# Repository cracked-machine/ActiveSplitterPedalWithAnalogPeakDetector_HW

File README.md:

## Active 4-way splitter pedal with analog peak detector

Required Kicad Hardware library: https://github.com/cracked-machine/KicadLibrary

- Analog 1->4 splitter circuit with buffered input and output gain controls.
- Analog LED peak detector per output channel.
- Fits in a Hammond 1590BB enclosure (120mm x 95mm).

### System Overview

### Schematic

##### Top Level

##### Power Supply block

##### Buffer/Attenuator block

##### Peak Detector block

## 3D Renderings

__PCB 3D Render (top view)__

__PCB 3D Render (bottom view)__

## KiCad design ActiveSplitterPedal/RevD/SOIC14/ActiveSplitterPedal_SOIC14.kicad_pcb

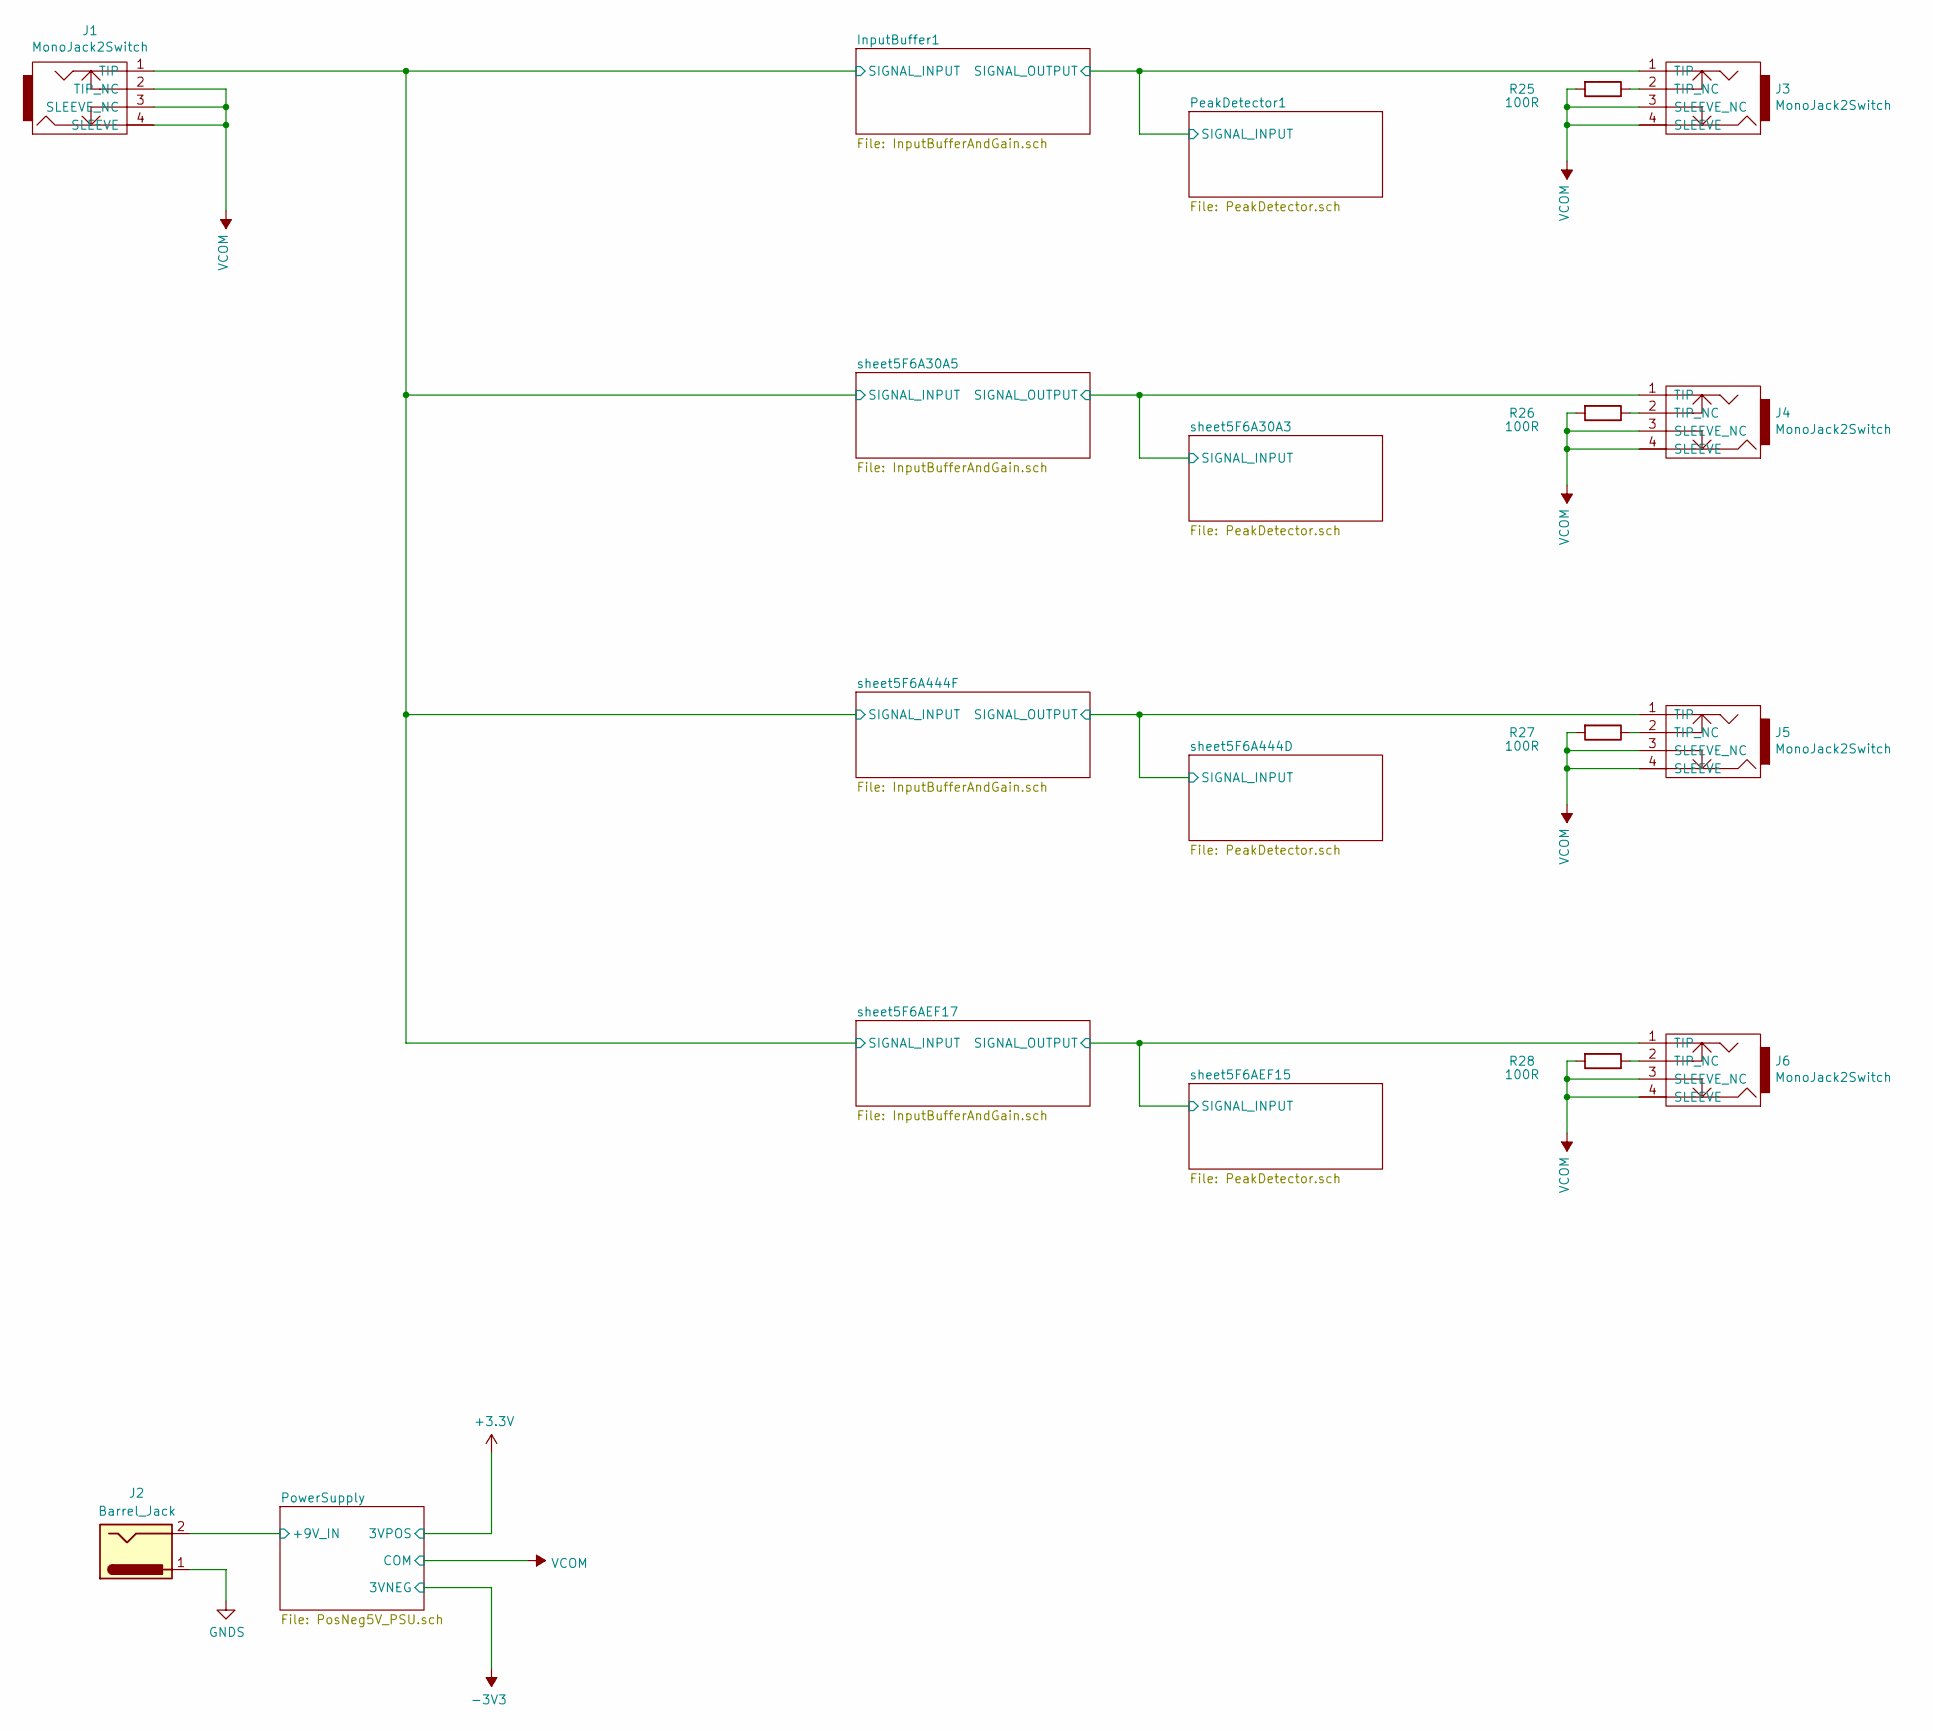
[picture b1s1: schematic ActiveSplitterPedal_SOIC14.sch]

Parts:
J1, J3, J4, J5, J6: MonoJack2Switch; NRJxHx
J2: Barrel_Jack; BarrelJack_Horizontal
R25, R26, R27, R28: 100R; C_0805_2012Metric_Pad1.15x1.40mm_HandSolder

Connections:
/InputBuffer1/SIGNAL_INPUT: J1.1 (TIP); also elsewhere on the board
/PeakDetector1/SIGNAL_INPUT: J3.1 (TIP); also elsewhere on the board
/PowerSupply/+9V_IN: J2.2; also elsewhere on the board
/sheet5F6A30A3/SIGNAL_INPUT: J4.1 (TIP); also elsewhere on the board
/sheet5F6A444D/SIGNAL_INPUT: J5.1 (TIP); also elsewhere on the board
/sheet5F6AEF15/SIGNAL_INPUT: J6.1 (TIP); also elsewhere on the board
GNDS: J2.1; also elsewhere on the board
unnamed: J3.2 (TIP_NC), R25.1
unnamed: J4.2 (TIP_NC), R26.1
unnamed: J5.2 (TIP_NC), R27.1
unnamed: J6.2 (TIP_NC), R28.1
VCOM: J1.2 (TIP_NC), J1.3 (SLEEVE_NC), J1.4 (SLEEVE), J3.3 (SLEEVE_NC), J3.4 (SLEEVE), J4.3 (SLEEVE_NC), J4.4 (SLEEVE), J5.3 (SLEEVE_NC), J5.4 (SLEEVE), J6.3 (SLEEVE_NC), J6.4 (SLEEVE), R25.2, R26.2, R27.2, R28.2; also elsewhere on the board

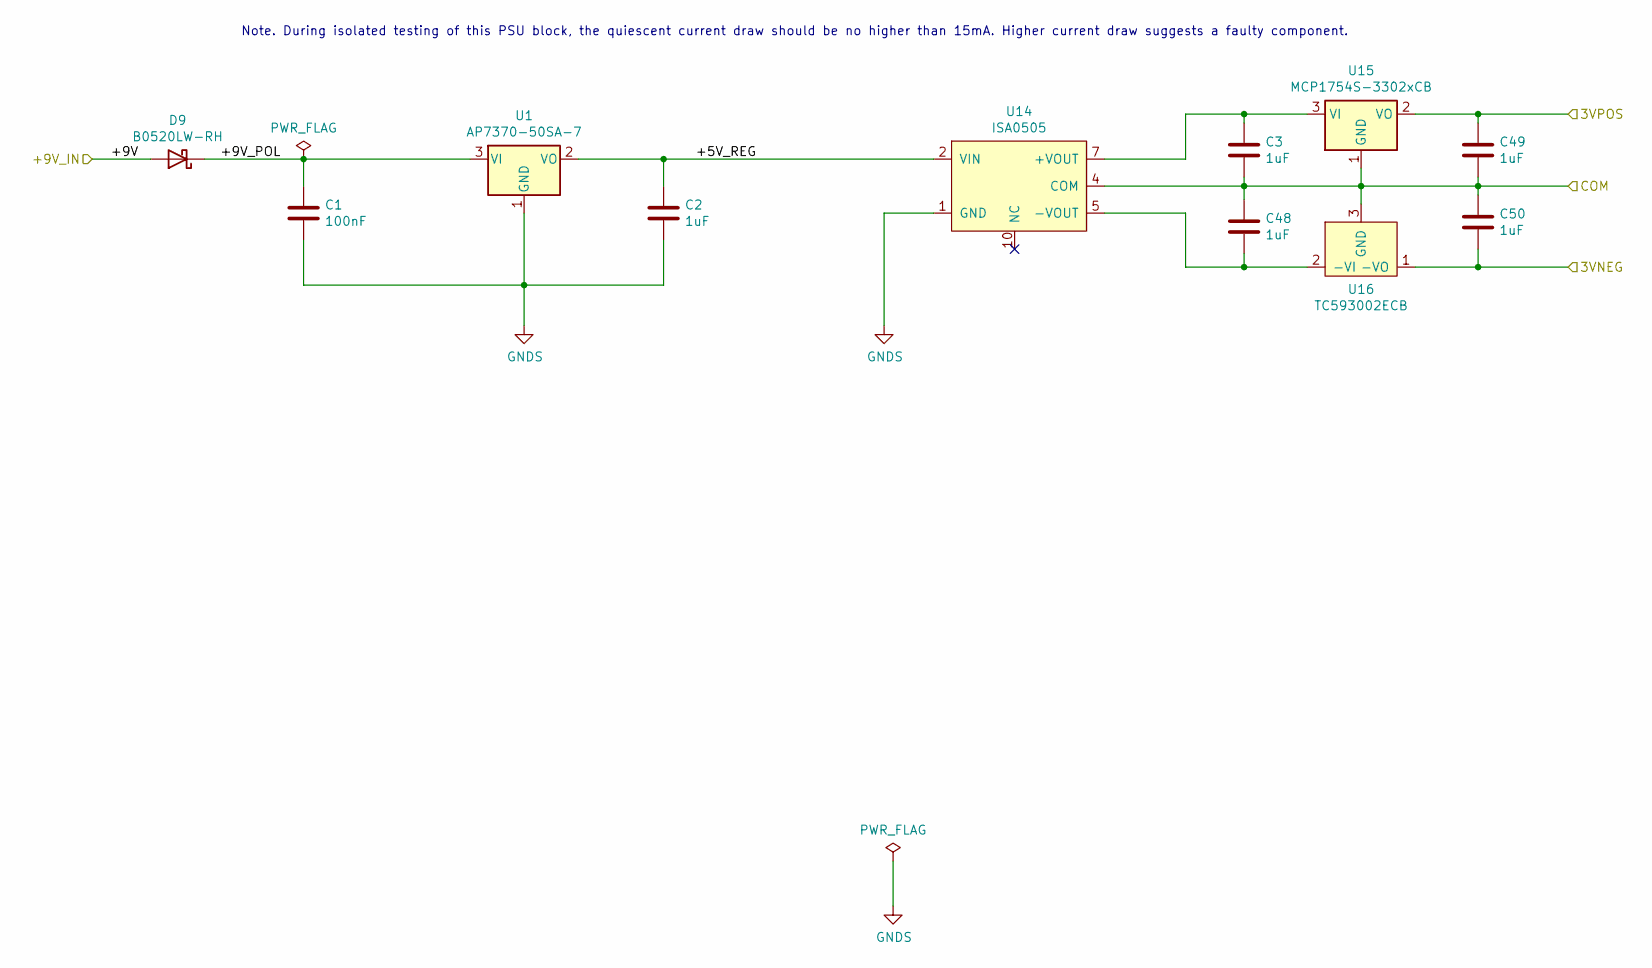
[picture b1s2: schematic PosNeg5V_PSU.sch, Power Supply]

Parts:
C1: 100nF; C_1206_3216Metric_Pad1.42x1.75mm_HandSolder
C2: 1uF; C_1206_3216Metric_Pad1.42x1.75mm_HandSolder
C3, C48, C49, C50: 1uF; C_0805_2012Metric_Pad1.15x1.40mm_HandSolder
D9: B0520LW-RH; D_SOD-123F
U1: AP7370-50SA-7; SOT-23
U14: ISA0505
U15: MCP1754S-3302xCB; SOT-23
U16: TC593002ECB; SOT-23

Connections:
+3V3: C49.1, U15.2 (VO); also elsewhere on the board
-3V3: C50.2, U16.1 (-VO); also elsewhere on the board
/PowerSupply/+5V_REG: C2.1, U1.2 (VO), U14.2 (VIN)
/PowerSupply/+9V_IN: D9.2 (A); also elsewhere on the board
/PowerSupply/+9V_POL: C1.1, D9.1 (K), U1.3 (VI)
GNDS: C1.2, C2.2, U1.1 (GND), U14.1 (GND); also elsewhere on the board
unnamed: C3.1, U14.7 (+VOUT), U15.3 (VI)
unnamed: C48.2, U14.5 (-VOUT), U16.2 (-VI)
VCOM: C3.2, C48.1, C49.2, C50.1, U14.4 (COM), U15.1 (GND), U16.3 (GND); also elsewhere on the board

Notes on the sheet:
Note. During isolated testing of this PSU block, the quiescent current draw should be no higher than 15mA. Higher current draw suggests a faulty component.

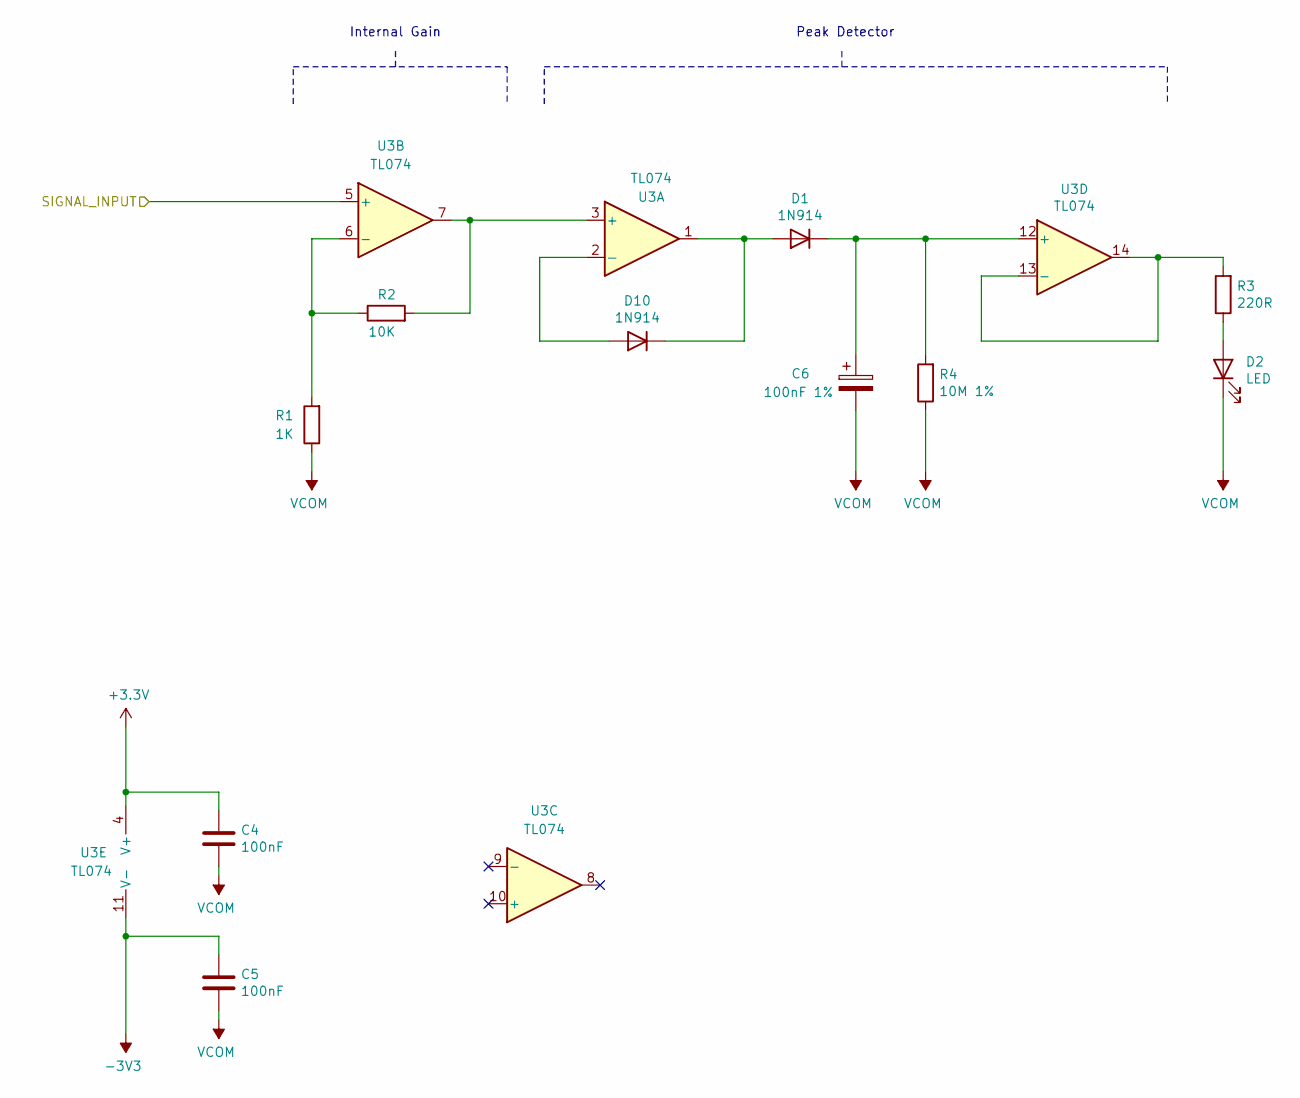
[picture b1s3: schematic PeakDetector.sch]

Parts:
C4, C5: 100nF; C_0805_2012Metric_Pad1.15x1.40mm_HandSolder
C6: 100nF 1%; C_1210_3225Metric_Pad1.42x2.65mm_HandSolder
D1, D10: 1N914; D_SOD-123F
D2: LED; LED_D5.0mm
R1: 1K; R_0805_2012Metric_Pad1.15x1.40mm_HandSolder
R2: 10K; R_0805_2012Metric_Pad1.15x1.40mm_HandSolder
R3: 220R; R_0805_2012Metric_Pad1.15x1.40mm_HandSolder
R4: 10M 1%; R_0805_2012Metric_Pad1.15x1.40mm_HandSolder
U3: TL074; SOIC-14_3.9x8.7mm_P1.27mm

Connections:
+3V3: C4.1, U3.4 (V+); also elsewhere on the board
-3V3: C5.1, U3.11 (V-); also elsewhere on the board
/PeakDetector1/SIGNAL_INPUT: U3.5 (+); also elsewhere on the board
unnamed: C6.1, D1.1 (K), R4.2, U3.12 (+)
unnamed: D1.2 (A), D10.1 (K), U3.1
unnamed: D2.2 (A), R3.1
unnamed: D10.2 (A), U3.2 (-)
unnamed: R1.2, R2.1, U3.6 (-)
unnamed: R2.2, U3.3 (+), U3.7
unnamed: R3.2, U3.13 (-), U3.14
VCOM: C4.2, C5.2, C6.2, D2.1 (K), R1.1, R4.1; also elsewhere on the board

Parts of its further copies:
C15, C16, C26, C27, C37, C38: 100nF; C_0805_2012Metric_Pad1.15x1.40mm_HandSolder
C17, C28, C39: 100nF 1%; C_1210_3225Metric_Pad1.42x2.65mm_HandSolder
D3, D5, D7, D11, D12, D13: 1N914; D_SOD-123F
D4, D6, D8: LED; LED_D5.0mm
R7, R13, R19: 1K; R_0805_2012Metric_Pad1.15x1.40mm_HandSolder
R8, R14, R20: 10K; R_0805_2012Metric_Pad1.15x1.40mm_HandSolder
R9, R15, R21: 220R; R_0805_2012Metric_Pad1.15x1.40mm_HandSolder
R10, R16, R22: 10M 1%; R_0805_2012Metric_Pad1.15x1.40mm_HandSolder
U6, U9, U12: TL074; SOIC-14_3.9x8.7mm_P1.27mm

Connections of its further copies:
+3V3: C15.1, C26.1, C37.1, U6.4 (V+), U9.4 (V+), U12.4 (V+); also elsewhere on the board
-3V3: C16.1, C27.1, C38.1, U6.11 (V-), U9.11 (V-), U12.11 (V-); also elsewhere on the board
/sheet5F6A30A3/SIGNAL_INPUT: U6.5 (+); also elsewhere on the board
/sheet5F6A444D/SIGNAL_INPUT: U9.5 (+); also elsewhere on the board
/sheet5F6AEF15/SIGNAL_INPUT: U12.5 (+); also elsewhere on the board
unnamed: C17.1, D3.1 (K), R10.2, U6.12 (+)
unnamed: C28.1, D5.1 (K), R16.2, U9.12 (+)
unnamed: C39.1, D7.1 (K), R22.2, U12.12 (+)
unnamed: D4.2 (A), R9.1
unnamed: D6.2 (A), R15.1
unnamed: D8.2 (A), R21.1
unnamed: D3.2 (A), D11.1 (K), U6.1
unnamed: D11.2 (A), U6.2 (-)
unnamed: D5.2 (A), D12.1 (K), U9.1
unnamed: D12.2 (A), U9.2 (-)
unnamed: D7.2 (A), D13.1 (K), U12.1
unnamed: D13.2 (A), U12.2 (-)
unnamed: R7.2, R8.1, U6.6 (-)
unnamed: R8.2, U6.3 (+), U6.7
unnamed: R9.2, U6.13 (-), U6.14
unnamed: R13.2, R14.1, U9.6 (-)
unnamed: R14.2, U9.3 (+), U9.7
unnamed: R15.2, U9.13 (-), U9.14
unnamed: R19.2, R20.1, U12.6 (-)
unnamed: R20.2, U12.3 (+), U12.7
unnamed: R21.2, U12.13 (-), U12.14
VCOM: C15.2, C16.2, C17.2, C26.2, C27.2, C28.2, C37.2, C38.2, C39.2, D4.1 (K), D6.1 (K), D8.1 (K), R7.1, R10.1, R13.1, R16.1, R19.1, R22.1; also elsewhere on the board

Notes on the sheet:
Internal Gain
Peak Detector

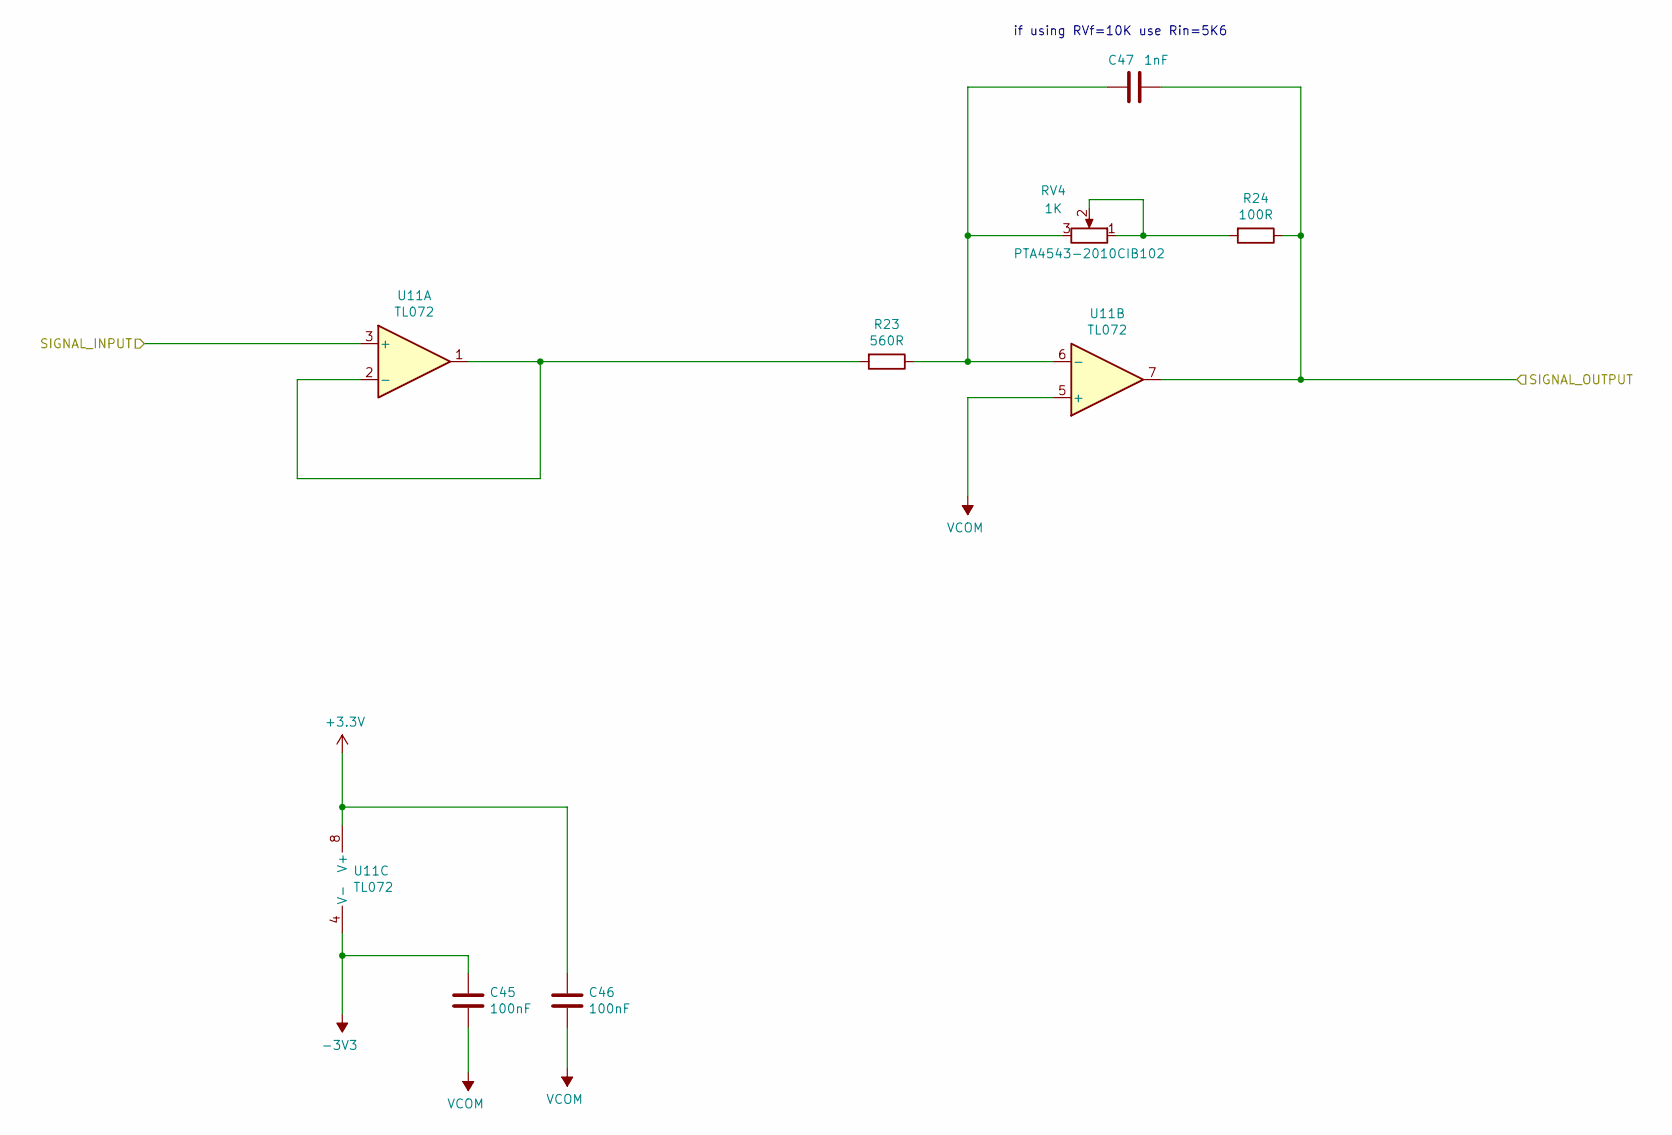
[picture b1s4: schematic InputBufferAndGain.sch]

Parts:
C12, C13: 100nF; C_0805_2012Metric_Pad1.15x1.40mm_HandSolder
C14: 1nF; C_0805_2012Metric_Pad1.15x1.40mm_HandSolder
R5: 560R; R_0805_2012Metric_Pad1.15x1.40mm_HandSolder
R6: 100R; R_0805_2012Metric_Pad1.15x1.40mm_HandSolder
RV1: 1K; Slider_PTA4543_60MM; Part No. PTA4543-2010CIB102
U2: TL072; SOIC-8_3.9x4.9mm_P1.27mm

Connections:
+3V3: C13.1, U2.8 (V+); also elsewhere on the board
-3V3: C12.1, U2.4 (V-); also elsewhere on the board
/InputBuffer1/SIGNAL_INPUT: U2.3 (+); also elsewhere on the board
/PeakDetector1/SIGNAL_INPUT: C14.1, R6.1, U2.7; also elsewhere on the board
unnamed: C14.2, R5.1, RV1.3, U2.6 (-)
unnamed: R5.2, U2.1, U2.2 (-)
unnamed: R6.2, RV1.1, RV1.2
VCOM: C12.2, C13.2, U2.5 (+); also elsewhere on the board

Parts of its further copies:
C23, C24, C34, C35, C45, C46: 100nF; C_0805_2012Metric_Pad1.15x1.40mm_HandSolder
C25, C36, C47: 1nF; C_0805_2012Metric_Pad1.15x1.40mm_HandSolder
R11, R17, R23: 560R; R_0805_2012Metric_Pad1.15x1.40mm_HandSolder
R12, R18, R24: 100R; R_0805_2012Metric_Pad1.15x1.40mm_HandSolder
RV2, RV3, RV4: 1K; Slider_PTA4543_60MM; Part No. PTA4543-2010CIB102
U5, U8, U11: TL072; SOIC-8_3.9x4.9mm_P1.27mm

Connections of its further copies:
+3V3: C24.1, C35.1, C46.1, U5.8 (V+), U8.8 (V+), U11.8 (V+); also elsewhere on the board
-3V3: C23.1, C34.1, C45.1, U5.4 (V-), U8.4 (V-), U11.4 (V-); also elsewhere on the board
/InputBuffer1/SIGNAL_INPUT: U5.3 (+), U8.3 (+), U11.3 (+); also elsewhere on the board
/sheet5F6A30A3/SIGNAL_INPUT: C25.1, R12.1, U5.7; also elsewhere on the board
/sheet5F6A444D/SIGNAL_INPUT: C36.1, R18.1, U8.7; also elsewhere on the board
/sheet5F6AEF15/SIGNAL_INPUT: C47.1, R24.1, U11.7; also elsewhere on the board
unnamed: C25.2, R11.1, RV2.3, U5.6 (-)
unnamed: C36.2, R17.1, RV3.3, U8.6 (-)
unnamed: C47.2, R23.1, RV4.3, U11.6 (-)
unnamed: R11.2, U5.1, U5.2 (-)
unnamed: R12.2, RV2.1, RV2.2
unnamed: R17.2, U8.1, U8.2 (-)
unnamed: R18.2, RV3.1, RV3.2
unnamed: R23.2, U11.1, U11.2 (-)
unnamed: R24.2, RV4.1, RV4.2
VCOM: C23.2, C24.2, C34.2, C35.2, C45.2, C46.2, U5.5 (+), U8.5 (+), U11.5 (+); also elsewhere on the board

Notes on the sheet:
if using RVf=10K use Rin=5K6

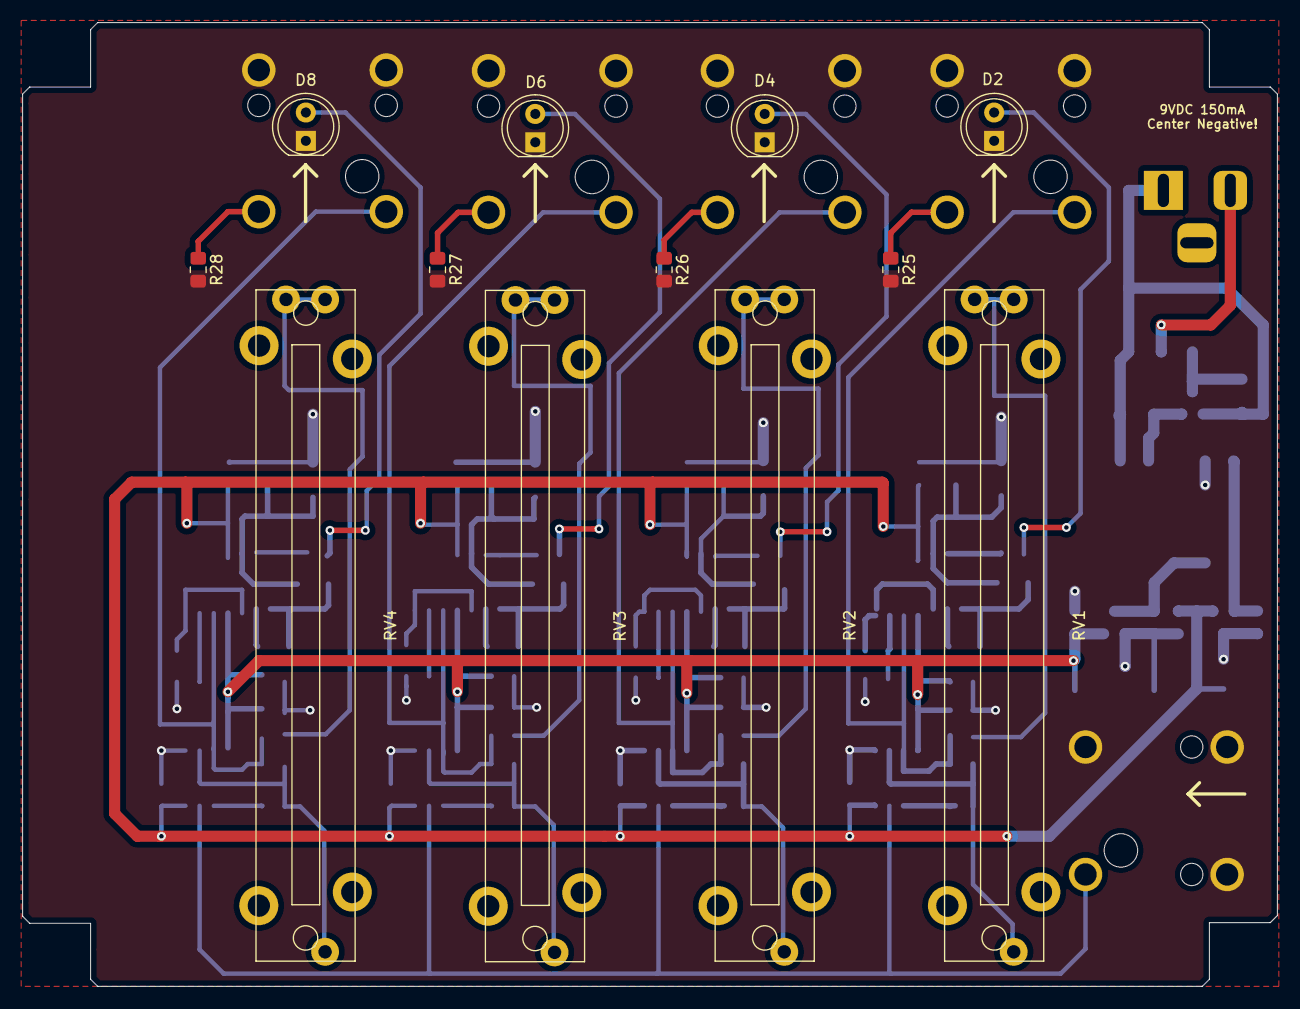
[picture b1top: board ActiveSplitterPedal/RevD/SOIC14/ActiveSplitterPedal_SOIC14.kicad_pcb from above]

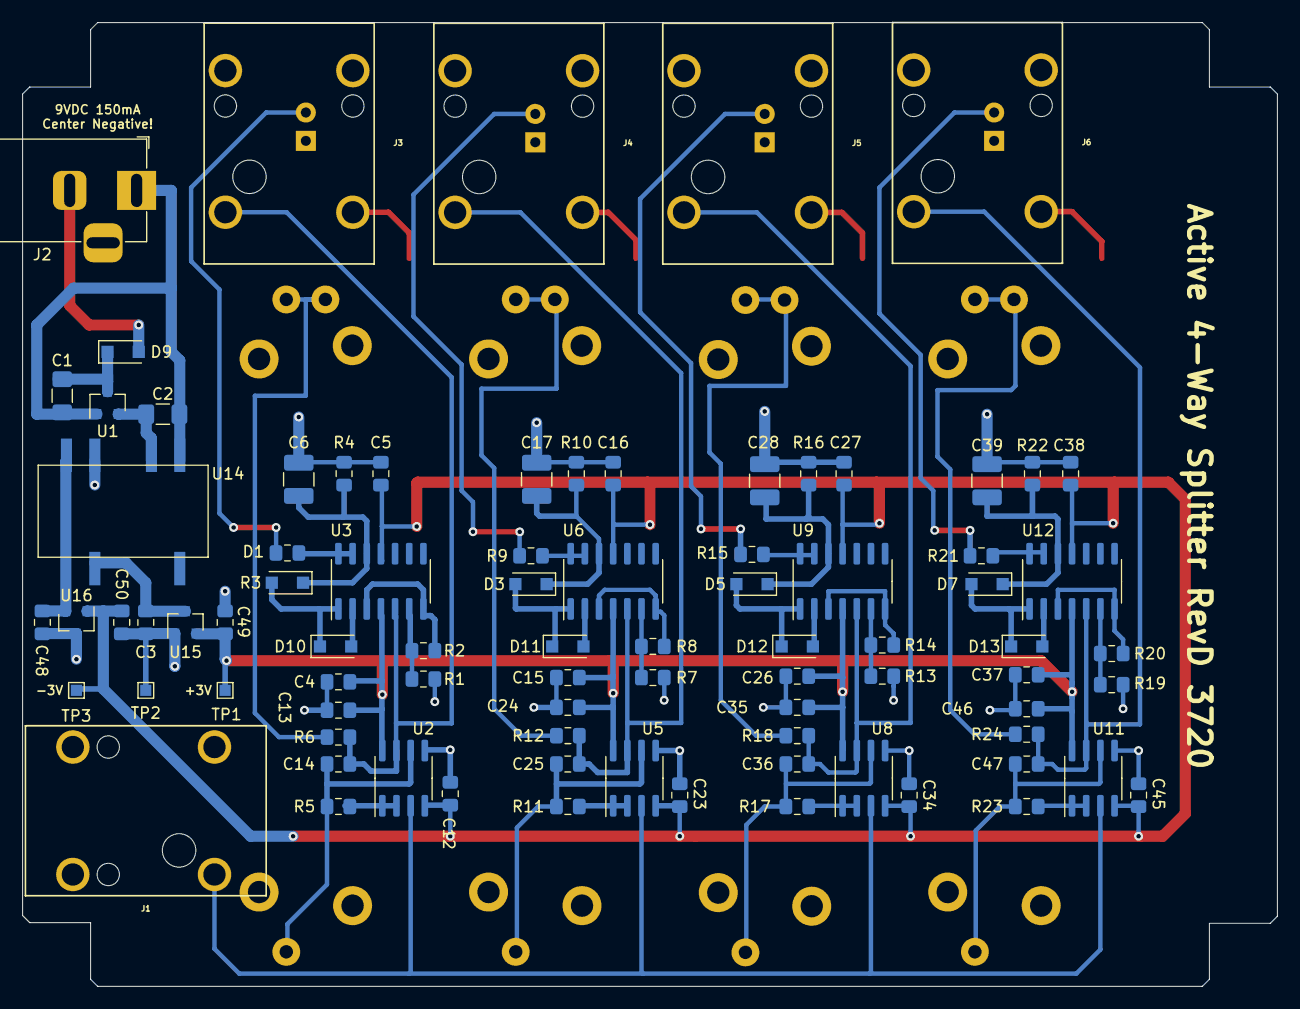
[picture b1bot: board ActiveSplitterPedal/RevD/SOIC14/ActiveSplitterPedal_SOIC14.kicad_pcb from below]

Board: 2 copper layers, 112.5 x 86.4 mm, 96 parts (84 on the bottom side), 58 nets.

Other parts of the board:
TP1, TP2, TP3: TestPoint; TestPoint_Pad_1.0x1.0mm

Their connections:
+3V3: TP1.1; also elsewhere on the board
-3V3: TP3.1; also elsewhere on the board
VCOM: TP2.1; also elsewhere on the board

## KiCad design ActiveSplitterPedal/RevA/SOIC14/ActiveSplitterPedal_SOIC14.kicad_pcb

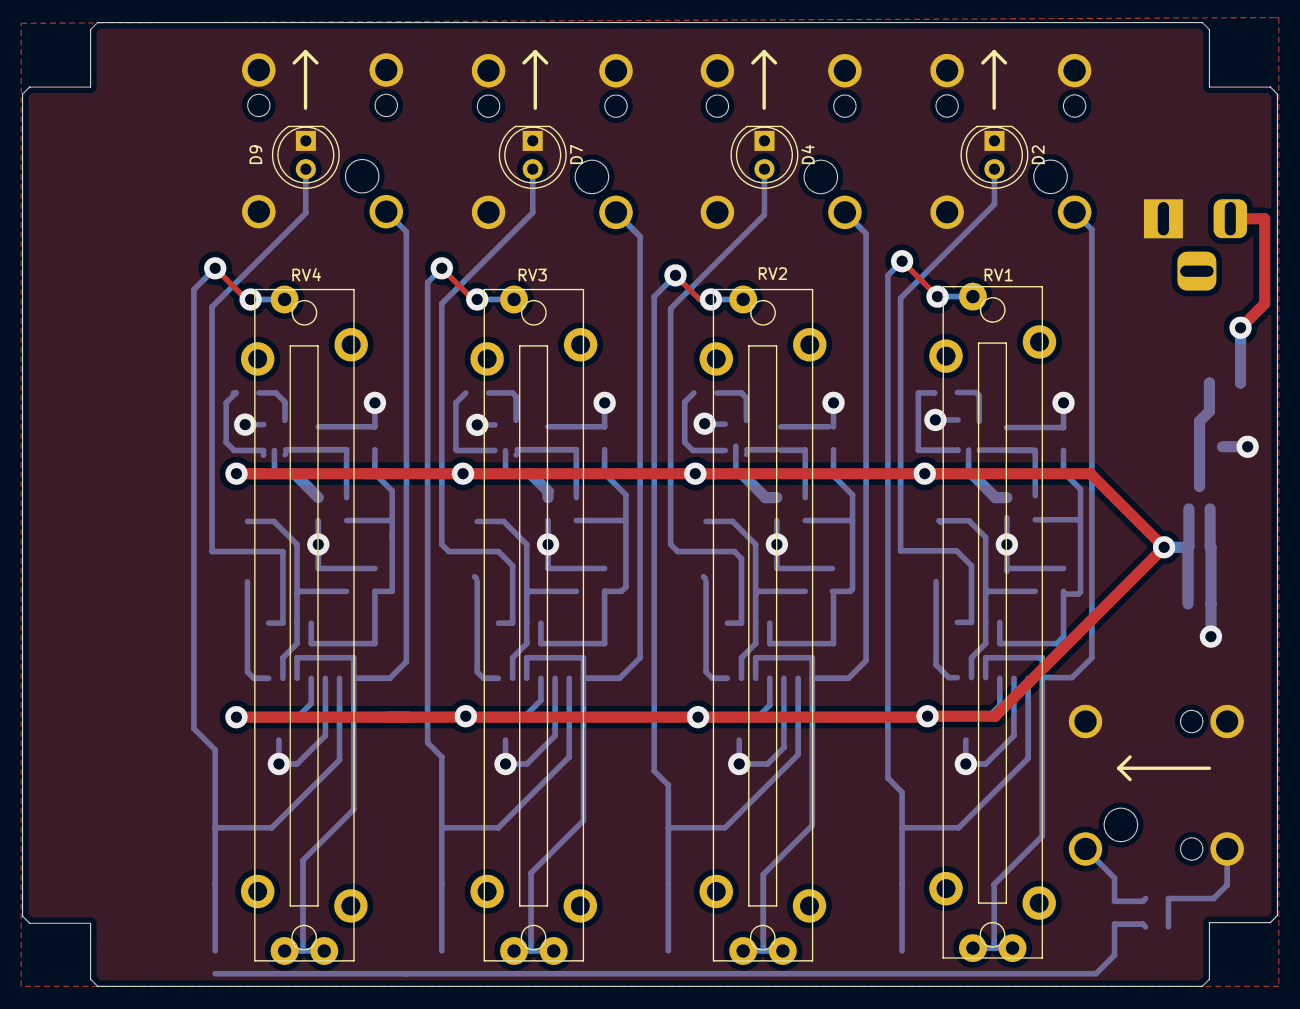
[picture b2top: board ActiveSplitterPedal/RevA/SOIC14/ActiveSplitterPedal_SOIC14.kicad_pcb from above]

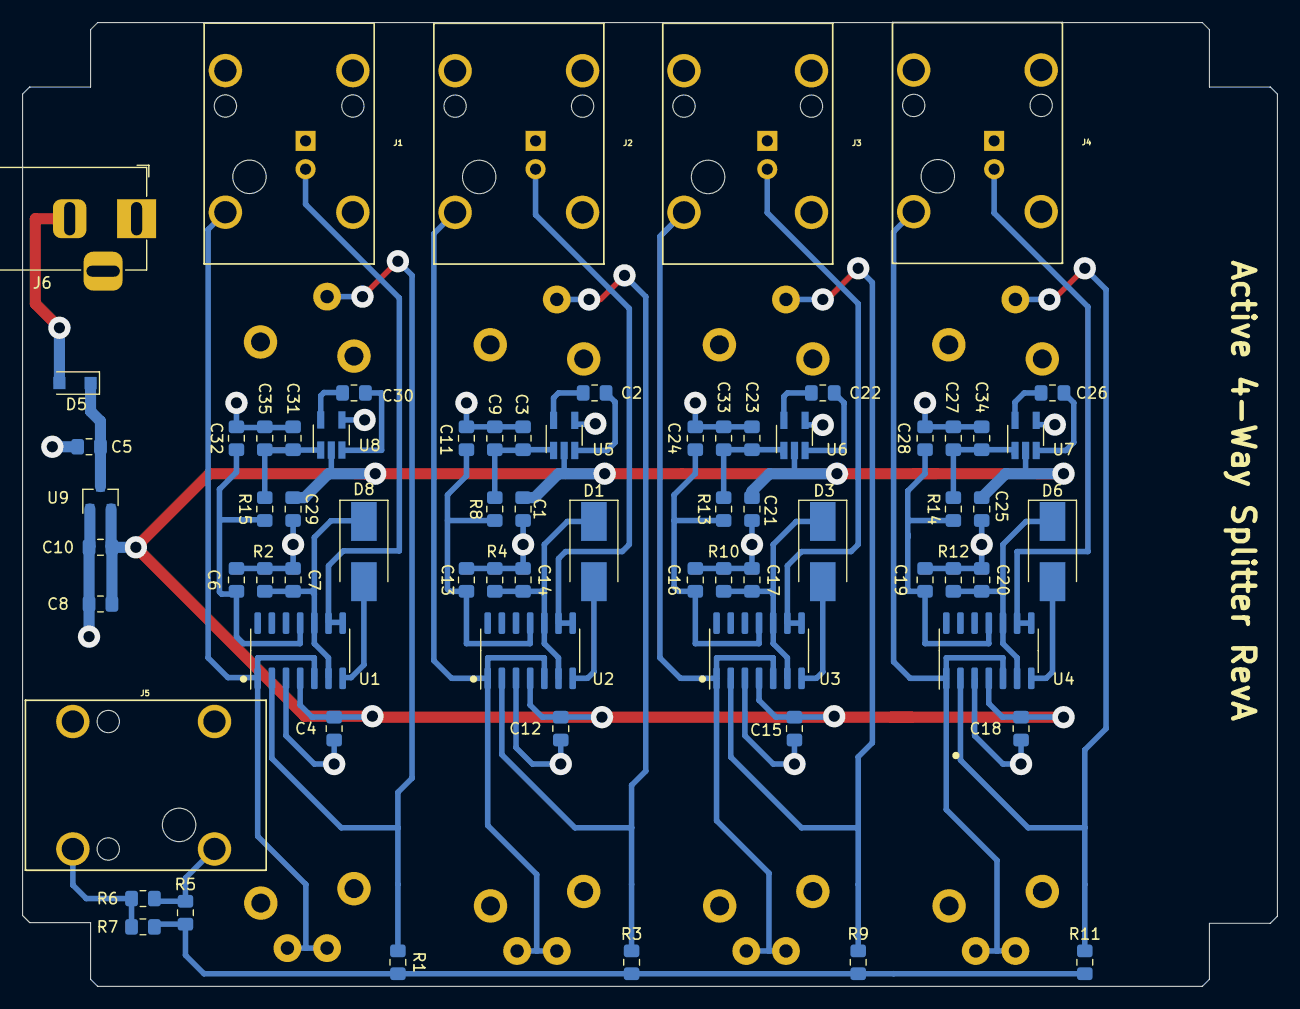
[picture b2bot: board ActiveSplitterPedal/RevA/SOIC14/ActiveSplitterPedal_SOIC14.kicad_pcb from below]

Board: 2 copper layers, 112.5 x 86.4 mm, 78 parts (70 on the bottom side), 42 nets.

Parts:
C1, C2, C4, C5, C6, C7, C9, C11, C12, C13, C14, C15, C16, C17, C18, C19, C20, C21, C22, C23, C24, C25, C26, C27, C28, C29, C30, C31, C32: 1uF; C_0805_2012Metric_Pad1.15x1.40mm_HandSolder
C3, C10, C33, C34, C35: 100nF; C_0805_2012Metric_Pad1.15x1.40mm_HandSolder
C8: 10uF; C_0805_2012Metric_Pad1.15x1.40mm_HandSolder
D1, D3, D6, D8: D_Schottky; D_SMB_Handsoldering
D2, D4, D7, D9: LED; LED_D5.0mm
D5: B0520LW-RH; D_SOD-123F
J1, J2, J3, J4, J5: MonoJack2Switch; NRJxHx
J6: Barrel_Jack; BarrelJack_Horizontal
R1, R3, R8, R9, R11, R13, R14, R15: 100R; R_0805_2012Metric_Pad1.15x1.40mm_HandSolder
R2, R4, R10, R12: 100K; R_0805_2012Metric_Pad1.15x1.40mm_HandSolder
R5: 10K; R_0805_2012Metric_Pad1.15x1.40mm_HandSolder
R6, R7: 2.2M; R_0805_2012Metric_Pad1.15x1.40mm_HandSolder
RV1, RV2, RV3, RV4: 1K; Slider_PTA4543_60MM
U1, U2, U3, U4: TL074; SOIC-14_3.9x8.7mm_P1.27mm
U5, U6, U7, U8: TPS60400; SOT-23-5_HandSoldering
U9: SE8250X2; SOT-23

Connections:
+5V: C1.1, C4.1, C8.1, C10.1, C12.1, C15.1, C18.1, C21.1, C25.1, C29.1, U1.4, U2.4, U3.4, U4.4, U5.2, U6.2, U7.2, U8.2, U9.2
/GainAndPeakDetector1/-5VOUT: C31.1, C35.1, R15.1, U8.1
/GainAndPeakDetector1/-5V_POL: C6.1, C32.1, R15.2, U1.11
/GainAndPeakDetector1/SIGNAL_INPUT: R1.2, R3.2, R5.1, R7.1, R9.2, R11.2
/GainAndPeakDetector1/SIGNAL_OUTPUT: J1.1, RV1.1, RV1.2, U1.1, U1.5
/GainAndPeakDetector2/-5VOUT: C3.1, C9.1, R8.1, U5.1
/GainAndPeakDetector2/-5V_POL: C11.1, C13.1, R8.2, U2.11
/GainAndPeakDetector2/SIGNAL_OUTPUT: J2.1, RV2.1, RV2.2, U2.1, U2.5
/GainAndPeakDetector3/-5VOUT: C23.1, C33.1, R13.1, U6.1
/GainAndPeakDetector3/-5V_POL: C16.1, C24.1, R13.2, U3.11
/GainAndPeakDetector3/SIGNAL_OUTPUT: J3.1, RV3.1, RV3.2, U3.1, U3.5
/GainAndPeakDetector4/-5VOUT: C27.1, C34.1, R14.1, U7.1
/GainAndPeakDetector4/-5V_POL: C19.1, C28.1, R14.2, U4.11
/GainAndPeakDetector4/SIGNAL_OUTPUT: J4.1, RV4.1, RV4.2, U4.1, U4.5
/PowerSupply/+9V_IN: D5.2, J6.2
/PowerSupply/+9V_POL: C5.1, D5.1, U9.3
GNDS: C1.2, C3.2, C4.2, C5.2, C6.2, C7.2, C8.2, C9.2, C10.2, C11.2, C12.2, C13.2, C14.2, C15.2, C16.2, C17.2, C18.2, C19.2, C20.2, C21.2, C23.2, C24.2, C25.2, C27.2, C28.2, C29.2, C31.2, C32.2, C33.2, C34.2, C35.2, D2.1, D4.1, D7.1, D9.1, J1.2, J1.3, J1.4, J2.2, J2.3, J2.4, J3.2, J3.3, J3.4, J4.2, J4.3, J4.4, J5.2, J5.3, J5.4, J6.1, R2.1, R4.1, R6.2, R7.2, R10.1, R12.1, U1.3, U2.3, U3.3, U4.3, U5.4, U6.4, U7.4, U8.4, U9.1
unnamed: C2.1, U5.3
unnamed: C2.2, U5.5
unnamed: C7.1, D8.1, R2.2, U1.6, U1.10
unnamed: C14.1, D1.1, R4.2, U2.6, U2.10
unnamed: C17.1, D3.1, R10.2, U3.6, U3.10
unnamed: C20.1, D6.1, R12.2, U4.6, U4.10
unnamed: C22.1, U6.3
unnamed: C22.2, U6.5
unnamed: C26.1, U7.3
unnamed: C26.2, U7.5
unnamed: C30.1, U8.3
unnamed: C30.2, U8.5
unnamed: D1.2, U2.7
unnamed: D2.2, U1.8, U1.9
unnamed: D3.2, U3.7
unnamed: D4.2, U2.8, U2.9
unnamed: D6.2, U4.7
unnamed: D7.2, U3.8, U3.9
unnamed: D8.2, U1.7
unnamed: D9.2, U4.8, U4.9
unnamed: J5.1, R5.2, R6.1
unnamed: R1.1, RV1.3, U1.2
unnamed: R3.1, RV2.3, U2.2
unnamed: R9.1, RV3.3, U3.2
unnamed: R11.1, RV4.3, U4.2
